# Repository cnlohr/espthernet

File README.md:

# espthernet

*It's pronounced "e-s-peethernet" - a party trick, not a legitimate engineering solution.*

ESP8266 + I2S = Software-based 10-Base-T Ethernet Driver

For a detailed overview of how this project works, please see the [Hackaday article](http://hackaday.com/2016/04/01/ethernet-controller-discovered-in-the-esp8266/).  For a rough idea of what's going on, checkout the youtube video:

## Overall Discussion

This is a relatively unreliable and coincidentally functional ESP8266 Ethernet driver.  It only uses two pins on the ESP, the I2S pins, but does provide Ethernet.  It does all its own manchester encoding/decoding, framing, FCS, etc.  It mimics the ENC424J600 stack found in [avrcraft](http://github.com/cnlohr/avrcraft) and borrows the IP, ARP, UDP and TCP stacks from that project, too.

This product was created by Charles Lohr, but, will likely fall out of support by original author quickly.  Additional contributers would be welcome.

The frontend [i2sduplex.c](user/i2sduplex.c) is what takes the bits off wire and calls a callback in an interrupt with raw 32-bit words of what came in from the wire.  It also accepts buffers to send raw bits out on the wire.

Though designed for the ESP8266 should be relatively portable, as most of the code is limited to [manchestrate.c](user/manchestrate.c) and related files.  Since it is designed to operate at full duplex, it is expecting a 40MHz-in, and 40MHz-out stream.  This stream mus be biased toward 0's instead of 1's since at 40MHz-in there are ambiguous bit patterns if you don't bias.  This takes on raw on-wire bits and puts out ethernet frames - or accepts frames and outputs raw on-wire bits.

From there, we can check the FCS and process the packets in a consistent way and have a way of interacting with buffers. [net_compat.c](etherhelp/net_compat.c) is what handles all of that.  The interface it provides mimics the ENC424J600 and is what is used in avrcraft.  The reason I use that interface on so many projects is because the style of memory access and use makes it require less buffers and less copying than stacks like lwip.

For the user layer, this system just borrows everything from avrcraft, including the http server!  You will notice that it's a little awkward since it's designed to operate with either the TCP/IP stack from Espressif OR the avrcraft TCP/IP server.  It would be really cool if we could figure out some way to have consistent entry.

## The Web Interface

There is a web interface that gets put on the ESPs with a "make" step from the "web" directory.  It pushes the webpage to the ESP.  The webpage does not need to live on the ESP, itself, it can be viewed independent of one, it just only supports the "Load Test Packet" feature in "Last Packet" [version on github.io](http://cnlohr.github.io/espthernet/web/page/). 

The webpage is what is used to look at packets, create the demanchestration table, [demanchestrate_table.h](user/demanchestrate_table.h) and test the table on new data.  This was needed considering how complicated the decoding process is.  Without testing on data, a lot of data, coming up with a robust algorithm was almost impossible!!! One other feature in the web interface is you can click on the 1's and 0's and turn them on and off to see how the system decodes those packets.

## Hardware

Option 1: ***recommended*** Use a line driver like the ILS3371 and ethernet magnetics and terminator.  This is superior, and likely to work in many situations except with stringent hardware and long cable runs. An example can be found in the [esp12e-ethernet.pdf](hardware/esp12e-ethernet.pdf).

Option 2: ***not recommended*** Just jam some capacitors and resistors onto the input and hope for the best.  This is potentially hazardous and may not work on many devices.  Be ready to be disappointed.

<A HREF="hardware/nodemcu-ethernet.png"></a>

Overall, just about any 10 mbit magnetics should do, and line drivers make things a lot better, especially if they have a bandwidth of 20 MHz.  Note that you absolutely must bias the incoming signal toward 0, so there will be slightly more 0's on the input stream than 1's.

## More to come?

Who knows?  Depending on how this is received I may work to improve and document it, but it was a lot of work and after months of this, I'm sick of it.

## License

This software is licensed under the 2-clause BSD license.  See "LICENSE" for more information

## Future Work
 * Switch to half-duplex option, or separate streams.  By using 20 MHz TX, and 32-36 MHz RX, you can save a lot of time since you'd have to process less data, and remove the requirement for signal bias. 
 * Add Hook to internal IP stack of whatever is being used.
 * Use FLPs instead of NLPs to negotiate for 10BaseT-FD instead of -HD  (Stack handles full duplex comms, no reason not to comm at it)
 * Use a pseudo-PLL for decoding packets rather than a transition finder.  It may be better?  Right now we monitor all transitions, instead we could look where we expect a bit transition and see what it does.

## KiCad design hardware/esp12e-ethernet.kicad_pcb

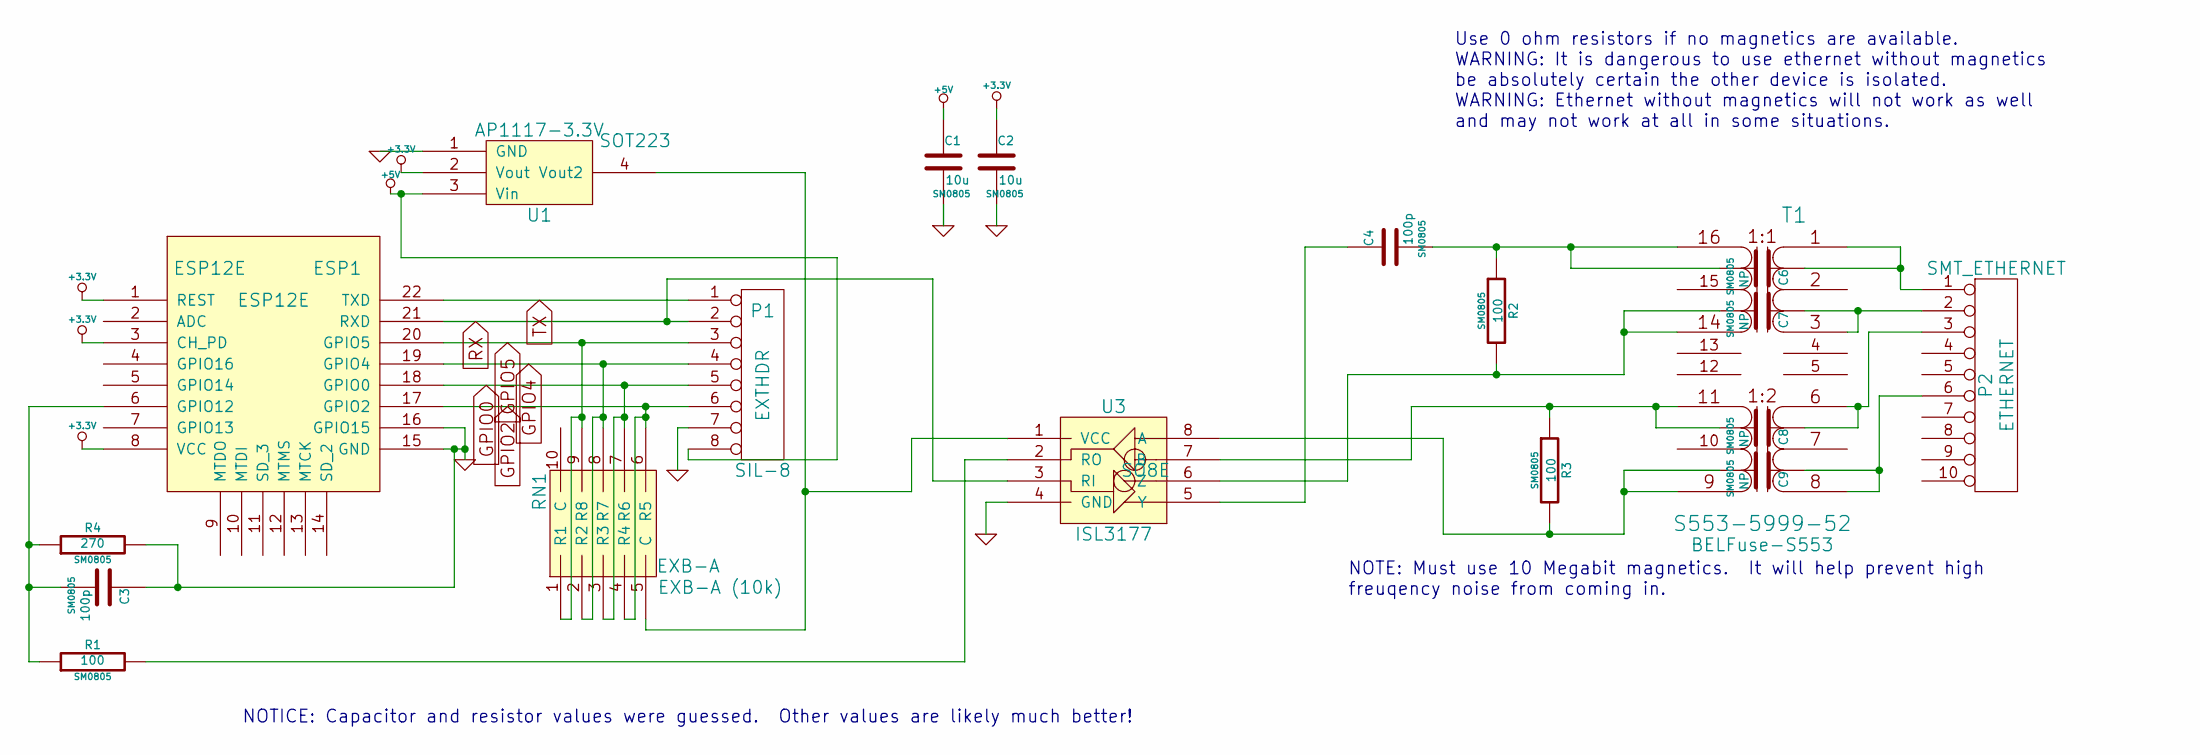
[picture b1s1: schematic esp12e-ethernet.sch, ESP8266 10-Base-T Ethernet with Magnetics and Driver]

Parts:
C1, C2: 10u; SM0805
C3, C4: 100p; SM0805
C6, C7, C8, C9: NP; SM0805
ESP1: ESP12E
P1: EXTHDR; SIL-8
P2: ETHERNET; SMT_ETHERNET
R1, R2, R3: 100; SM0805
R4: 270; SM0805
RN1: EXB-A (10k); EXB-A
T1: S553-5999-52; BELFuse-S553
U1: AP1117-3.3V; SOT223
U3: ISL3177; SO8E

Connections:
+3.3V: C2.1, ESP1.1 (REST), ESP1.3 (CH_PD), ESP1.8 (VCC), U1.2 (Vout)
+5V: C1.1, P1.8, U1.3 (Vin)
GND: C1.2, C2.2, C3.1, ESP1.15 (GND), ESP1.16 (GPIO15), P1.7, R4.2, U1.1 (GND), U3.4 (GND)
GPIO0: ESP1.18 (GPIO0), P1.5, RN1.3 (R3), RN1.7 (R6)
GPIO2: ESP1.17 (GPIO2), P1.6, RN1.4 (R4), RN1.6 (R5)
GPIO4: ESP1.19 (GPIO4), P1.4, RN1.2 (R2), RN1.8 (R7)
GPIO5: ESP1.20 (GPIO5), P1.3, RN1.1 (R1), RN1.9 (R8)
unnamed: C7.1, P2.2, T1.3 (PR2)
unnamed: C9.2, R3.2, T1.9 (S1), U3.8 (A)
unnamed: C9.1, P2.6, T1.8 (PR2)
unnamed: C8.1, P2.3, T1.6 (PR1)
unnamed: C6.1, P2.1, T1.1 (RX1)
unnamed: C4.2, C6.2, R2.1, T1.16 (S2)
unnamed: C8.2, R3.1, T1.11 (S2), U3.7 (B)
unnamed: C7.2, R2.2, T1.14 (S1), U3.6 (Z)
unnamed: C4.1, U3.5 (Y)
unnamed: R1.2, U3.2 (RO)
unnamed: C3.2, ESP1.6 (GPIO12), R1.1, R4.1
unnamed: RN1.5 (C), U1.4 (Vout2), U3.1 (VCC)
RX: ESP1.21 (RXD), P1.2, U3.3 (RI)
TX: ESP1.22 (TXD), P1.1

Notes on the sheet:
Use 0 ohm resistors if no magnetics are available. WARNING: It is dangerous to use ethernet without magnetics be absolutely certain the other device is isolated. WARNING: Ethernet without magnetics will not work as well and may not work at all in some situations.
NOTICE: Capacitor and resistor values were guessed. Other values are likely much better!
NOTE: Must use 10 Megabit magnetics. It will help prevent high freuqency noise from coming in.

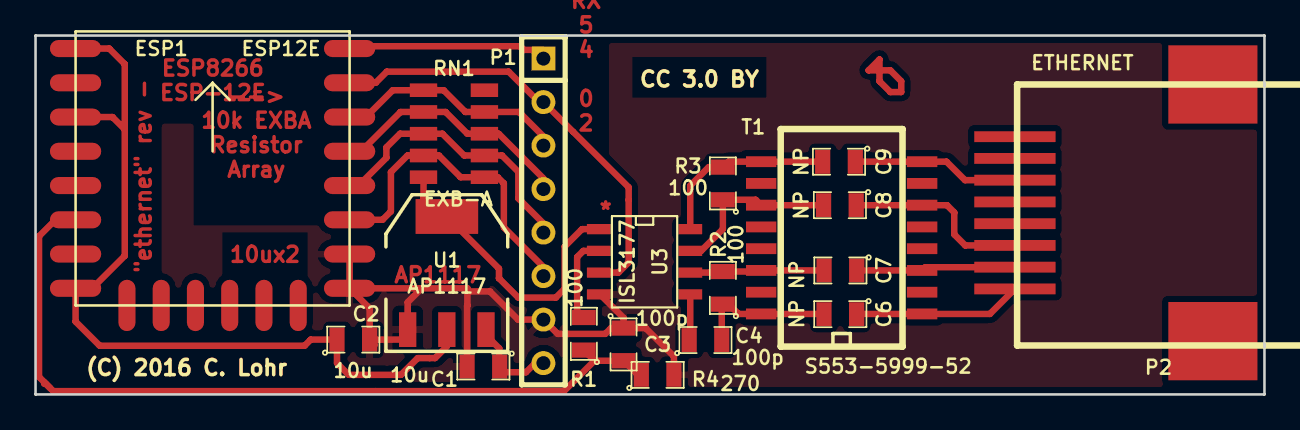
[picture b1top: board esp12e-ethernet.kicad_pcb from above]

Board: 2 copper layers, 71.8 x 21.0 mm, 19 parts (0 on the bottom side), 21 nets.

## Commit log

2016-03-27 Initial, rough-draft commit.
2016-03-27 new git ignore!
2016-03-27 add git attributes
2016-03-27 update linguist file
2016-03-27 update vendered file
2016-03-27 playing with readme
2016-03-27 More updates to webpage, etc.
2016-03-27 general updates to appearance of webpage
2016-03-27 Add index test
2016-03-27 update index/main
2016-03-27 remove index
2016-03-27 Update page interface
2016-03-27 add gitignore and update for manchestrate, pushing the demanchestration code as far as we can.
2016-03-27 Pushing the boundaries on performance
2016-03-28 Ok, high performance demanchestrate
2016-03-28 major overhaul - make everything execute on new data coming in pipe.
2016-03-28 further general progress. Still cleaning things up.
2016-03-28 getting closer...
2016-03-28 yigh maybe this is as good as it's gonna be
2016-03-29 YAY More reliable TX
2016-03-29 remove lockout on service now that we've switched to a NLP
2016-03-29 closing in on the missing bytes.
2016-03-29 Functional, about 99.5% packet passing.
2016-03-29 Add tabled crc32 there goes another 512 bytes of ram :(
2016-03-29 forgot to commit the actual crc32s
2016-03-29 Ok, got the whole monitoring packets working, too... Can reflash from anything.
2016-03-29 TCP almost there, few more bugs to iron out.
2016-03-29 AAALLMMOOOSSTTT
2016-03-29 add todo
2016-03-29 another warning
2016-03-30 refactor, clean up flash rewriter... Rework the way nlps are sent.
2016-03-31 add notes
2016-03-31 Update the hardware folder with current hardware designs
2016-04-01 Major documentation changes!
2016-04-01 Add janky circuit schematic.
2016-04-01 Try to fix up links, etc.
2016-04-01 fix schematic image.
2016-04-01 try this for an image?
2016-04-01 trying this for a link. Good grief I am bad at learning how to markdown
2016-04-01 try this for an image
2016-04-01 OK maybe this'll work.
2016-04-01 maybe putting the alt text in will fix it?
2016-04-01 maybe this syntax?
2016-04-01 no immediate alt?
2016-04-01 try HTML?
2016-04-01 Relative paths may work?
2016-04-01 try bold text
2016-04-01 Update readme with webpage information
2016-04-01 fix up some descriptions and fix location of slc_register.h
2016-04-01 change user mode to the system default for public use.
2016-04-01 cleanup packetmater and document more of custom_commands.c
2016-04-02 Fix possible intonation bug + Change trailer to 0xfff00000. This seems to have dramatic improvements on the magneticless systems.
2016-04-02 update schematic with better design
2016-04-05 General updates, allow for TCP-specific, non-HTTP servers to enable remote capture of ports.
    For more information on that, check out the pRemoteSniffer section
2016-04-07 Add the bin's for other people to play with.
2016-04-12 rework Makefiles to behave better and be more configurable, also remove dependency on fw_tool
2016-04-12 remove old binaries
2017-04-17 Fix broken Markdown headings
2017-05-23 tiny performance increase.

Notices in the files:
hardware/esp12e-ethernet.kicad_pcb:
(C) 2016 C. Lohr
hardware/esp12e-ethernet.sch:
(C) 2016 < Charles Lohr
